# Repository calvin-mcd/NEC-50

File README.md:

# NEC-50

NEC-50 is a katana stagger keyboard pcb using the micro controller [rp2040-zero](https://www.waveshare.com/rp2040-zero.htm) and taking heavy inspiration from the [NEC PC-9801](http://xahlee.info/kbd/nec_m_type_1992.html)

## Layout

[Link](http://www.keyboard-layout-editor.com/#/gists/75caf7895b6885905f6ad9112279089a)

## Cases

There are two cases for the NEC-50 so far:

- BAonDiscord#7634's custom case is called the N0550 and takes inspiration from the M0110.

https://github.com/ba-keyboards/N0550

check out their other amazing cases here: https://ba-keyboards.github.io/

- dingusaurusderp's case is called the Hotdog stand (lol) and is a two piece and can also support a weight if desired!

https://www.printables.com/de/model/784448-hotdog-stand-nec-50-case
  
## Disclaimer

The PCB and case files has been fully tested and confirmed to work. The members of the PCB development team are however not liable if you end up with a non-functional pcb. Order at your own risk. Support will not be provided but pull requests will be reviewed and possibly accepted.

## License

This project is released under the GPL v3 License. Please refer to the LICENCE file.

## Credits

big thanks to both BAonDiscord#7634 and dingusaurusderp for taking their time to create unqiue cases for something that started out as more of a joke! love the 40s community!

also many thanks to haizeus for helping with the KLE and firmware!

As always big thanks also to the many people who inspired and helped with this board!

Any questions, contact Calvin\#0563 on Discord.

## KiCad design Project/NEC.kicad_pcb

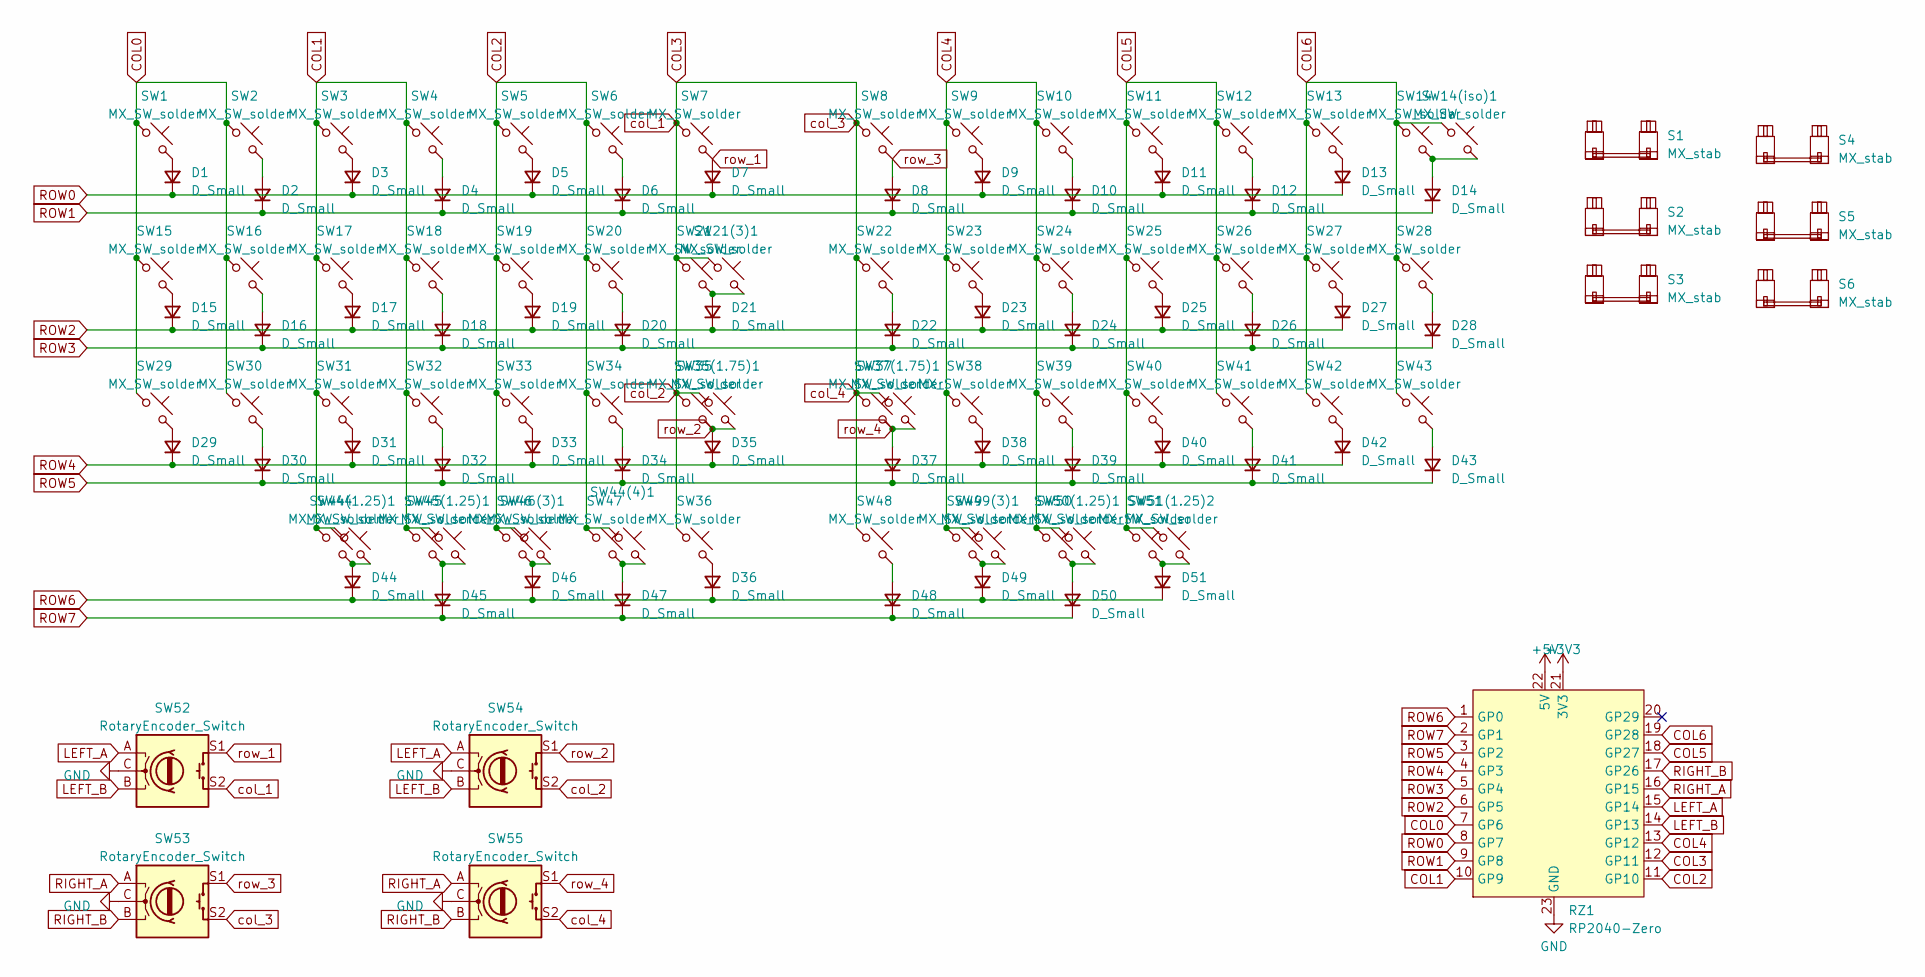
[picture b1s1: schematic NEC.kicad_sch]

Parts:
D1, D2, D3, D4, D5, D6, D7, D8, D9, D10, D11, D12, D13, D14, D15, D16, D17, D18, D19, D20, D21, D22, D23, D24, D25, D26, D27, D28, D29, D30, D31, D32, D33, D34, D35, D36, D37, D38, D39, D40, D41, D42, D43, D44, D45, D46, D47, D48, D49, D50, D51: D_Small; Diode-Hybrid-Back
RZ1: RP2040-Zero
S1, S2: MX_stab; STAB_MX_P_2u
S3, S4, S5: MX_stab; STAB_MX_3u
S6: MX_stab; STAB_MX_ISO_FLIPPED
SW1, SW14, SW21, SW22, SW29, SW36, SW43, SW45, SW46, SW49, SW50: MX_SW_solder; SW_MX_1.5u
SW2, SW3, SW4, SW5, SW6, SW9, SW10, SW11, SW12, SW13, SW14(iso)1, SW16, SW17, SW18, SW19, SW20, SW21(3)1, SW23, SW24, SW25, SW26, SW27, SW30, SW31, SW32, SW33, SW34, SW35, SW37, SW38, SW39, SW40, SW41, SW42, SW44, SW46(3)1, SW47, SW48, SW49(3)1, SW51: MX_SW_solder; SW_MX_1u
SW7, SW8, SW15, SW28, SW44(1.25)1, SW45(1.25)1, SW50(1.25)1, SW51(1.25)2: MX_SW_solder; SW_MX_1.25u
SW35(1.75)1, SW37(1.75)1: MX_SW_solder; SW_MX_1.75u
SW44(4)1: SW_Push_45deg; CherryMX_4.00u
SW52, SW53, SW54, SW55: RotaryEncoder_Switch; ROT_Alps_EC11E-Switch

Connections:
+3V3: RZ1.21 (3V3)
+5V: RZ1.22 (5V)
COL0: RZ1.7 (GP6), SW1.1, SW2.1, SW15.1, SW16.1, SW29.1, SW30.1
COL1: RZ1.10 (GP9), SW3.1, SW4.1, SW17.1, SW18.1, SW31.1, SW32.1, SW44.1, SW44(1.25)1.1, SW45.1, SW45(1.25)1.1
COL2: RZ1.11 (GP10), SW5.1, SW6.1, SW19.1, SW20.1, SW33.1, SW34.1, SW44(4)1.1, SW46.1, SW46(3)1.1, SW47.1
COL3: RZ1.12 (GP11), SW7.1, SW8.1, SW21.1, SW21(3)1.1, SW22.1, SW35.1, SW35(1.75)1.1, SW36.1, SW37.1, SW37(1.75)1.1, SW48.1, SW52.S2, SW53.S2, SW54.S2, SW55.S2
COL4: RZ1.13 (GP12), SW9.1, SW10.1, SW23.1, SW24.1, SW38.1, SW39.1, SW49.1, SW49(3)1.1, SW50.1, SW50(1.25)1.1
COL5: RZ1.18 (GP27), SW11.1, SW12.1, SW25.1, SW26.1, SW40.1, SW41.1, SW51.1, SW51(1.25)2.1
COL6: RZ1.19 (GP28), SW13.1, SW14.1, SW14(iso)1.1, SW27.1, SW28.1, SW42.1, SW43.1
GND: RZ1.23 (GND), SW52.C, SW53.C, SW54.C, SW55.C
LEFT_A: RZ1.15 (GP14), SW52.A, SW54.A
LEFT_B: RZ1.14 (GP13), SW52.B, SW54.B
unnamed: D1.2 (A), SW1.2
unnamed: D2.2 (A), SW2.2
unnamed: D3.2 (A), SW3.2
unnamed: D4.2 (A), SW4.2
unnamed: D5.2 (A), SW5.2
unnamed: D6.2 (A), SW6.2
unnamed: D9.2 (A), SW9.2
unnamed: D10.2 (A), SW10.2
unnamed: D11.2 (A), SW11.2
unnamed: D12.2 (A), SW12.2
unnamed: D13.2 (A), SW13.2
unnamed: D14.2 (A), SW14.2, SW14(iso)1.2
unnamed: D15.2 (A), SW15.2
unnamed: D16.2 (A), SW16.2
unnamed: D17.2 (A), SW17.2
unnamed: D18.2 (A), SW18.2
unnamed: D19.2 (A), SW19.2
unnamed: D20.2 (A), SW20.2
unnamed: D21.2 (A), SW21.2, SW21(3)1.2
unnamed: D22.2 (A), SW22.2
unnamed: D23.2 (A), SW23.2
unnamed: D24.2 (A), SW24.2
unnamed: D25.2 (A), SW25.2
unnamed: D26.2 (A), SW26.2
unnamed: D27.2 (A), SW27.2
unnamed: D28.2 (A), SW28.2
unnamed: D29.2 (A), SW29.2
unnamed: D30.2 (A), SW30.2
unnamed: D31.2 (A), SW31.2
unnamed: D32.2 (A), SW32.2
unnamed: D33.2 (A), SW33.2
unnamed: D34.2 (A), SW34.2
unnamed: D36.2 (A), SW36.2
unnamed: D38.2 (A), SW38.2
unnamed: D39.2 (A), SW39.2
unnamed: D40.2 (A), SW40.2
unnamed: D41.2 (A), SW41.2
unnamed: D42.2 (A), SW42.2
unnamed: D43.2 (A), SW43.2
unnamed: D44.2 (A), SW44.2, SW44(1.25)1.2
unnamed: D45.2 (A), SW45.2, SW45(1.25)1.2
unnamed: D46.2 (A), SW46.2, SW46(3)1.2
unnamed: D47.2 (A), SW44(4)1.2, SW47.2
unnamed: D48.2 (A), SW48.2
unnamed: D49.2 (A), SW49.2, SW49(3)1.2
unnamed: D50.2 (A), SW50.2, SW50(1.25)1.2
unnamed: D51.2 (A), SW51.2, SW51(1.25)2.2
RIGHT_A: RZ1.16 (GP15), SW53.A, SW55.A
RIGHT_B: RZ1.17 (GP26), SW53.B, SW55.B
ROW0: D1.1 (K), D3.1 (K), D5.1 (K), D7.1 (K), D9.1 (K), D11.1 (K), D13.1 (K), RZ1.8 (GP7)
ROW1: D2.1 (K), D4.1 (K), D6.1 (K), D8.1 (K), D10.1 (K), D12.1 (K), D14.1 (K), RZ1.9 (GP8)
ROW2: D15.1 (K), D17.1 (K), D19.1 (K), D21.1 (K), D23.1 (K), D25.1 (K), D27.1 (K), RZ1.6 (GP5)
ROW3: D16.1 (K), D18.1 (K), D20.1 (K), D22.1 (K), D24.1 (K), D26.1 (K), D28.1 (K), RZ1.5 (GP4)
ROW4: D29.1 (K), D31.1 (K), D33.1 (K), D35.1 (K), D38.1 (K), D40.1 (K), D42.1 (K), RZ1.4 (GP3)
ROW5: D30.1 (K), D32.1 (K), D34.1 (K), D37.1 (K), D39.1 (K), D41.1 (K), D43.1 (K), RZ1.3 (GP2)
ROW6: D36.1 (K), D44.1 (K), D46.1 (K), D49.1 (K), D51.1 (K), RZ1.1 (GP0)
ROW7: D45.1 (K), D47.1 (K), D48.1 (K), D50.1 (K), RZ1.2 (GP1)
row_1: D7.2 (A), SW7.2, SW52.S1
row_2: D35.2 (A), SW35.2, SW35(1.75)1.2, SW54.S1
row_3: D8.2 (A), SW8.2, SW53.S1
row_4: D37.2 (A), SW37.2, SW37(1.75)1.2, SW55.S1

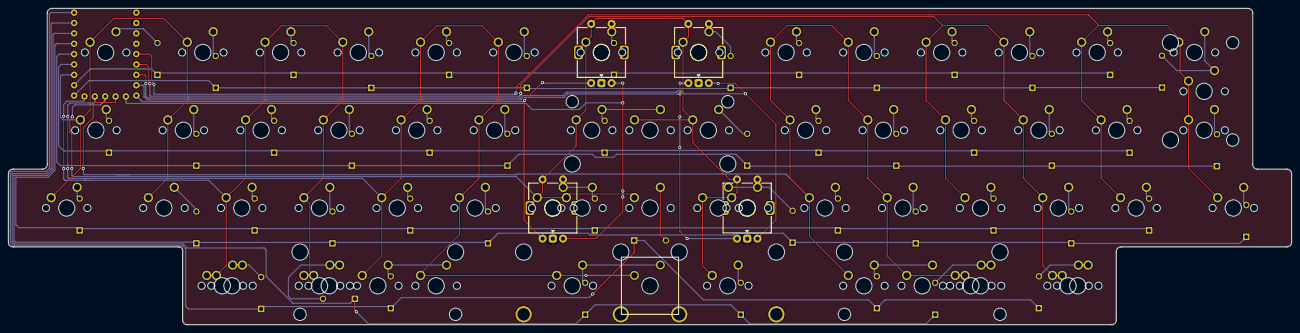
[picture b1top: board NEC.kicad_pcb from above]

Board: 2 copper layers, 314.3 x 77.5 mm, 124 parts (1 on the bottom side), 71 nets.

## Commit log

2023-03-04 initialise
2023-03-05 1st draft compete
2023-03-05 organised folders
2023-03-05 silkscreen, aesthetics, new production files
2023-03-05 clear up production files
2023-03-05 update render
2023-03-05 clean up
2023-03-10 silkscreen revision, some routing cleaning
2023-03-10 small silkscreen change
2023-04-01 backup
2023-04-22 jlcjlc text added, new production files
2023-05-17 fresh gerbers
2023-05-19 backups
2023-05-31 added 5 pin support for 4u centre switch
2023-06-13 added firmware (rotaries not tested yet)
2023-06-14 update readme & KLE
2023-06-14 KLE update
2023-06-14 update KLE
2023-06-14 readme update
2024-02-27 new case link added to readme
2024-02-27 clearer labelling on THT diodes & fresh gerbers
